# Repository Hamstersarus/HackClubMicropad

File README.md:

# HackClubMicropad

---

## Table of Contents

- [Overview](#overview)
- [Photos](#photos)
- [Bill of Materials](#bill-of-materials)

---

## Overview

The HackClub Micropad is a compact, USB-HID macropad intended for programmable shortcut input.
It was designed from scratch in KiCad and manufactured via JLCPCB. Firmware runs on CircuitPython.
It is a keybord with a programmable OLED screen, 6 keys, and a rotary encoder.
It is a fun, memorable, and beginner friendly productivity tool.

**Key features:**

- Seeed Studio XIAO RP2350 microcontroller
- Mechanical key switches (MX-compatible footprints)
- Rotary encoder with push-button
- Onboard NeoPixel (WS2812B) RGB indicator
- USB-C connectivity via the XIAO module
- 3D-printed enclosure (FDM, PLA)

---

## Photos

**PCB Top View**

**Assembled Board**

**Case**

---

### Bill of Materials

| Part Number | Description | Quantity | Ordering Location |
| :--- | :--- | :--- | :--- |
| 1597-102010550-ND | Seeed Studio XIAO RP2350 microcontroller (DIP) | 1 | [DigiKey](https://www.digikey.com/en/products/result?keywords=1597-102010550-ND) |
| 4809-EC11E15204A3-ND | EC11 rotary encoder with push-button, 5-pin | 1 | [DigiKey](https://www.digikey.com/en/products/detail/alps-alpine/EC11E15204A3/21721644) |
| 3086-MDOB128064V2V-YI-ND | SSD1306 OLED Screen | 1 | [DigiKey](https://www.digikey.com/en/products/detail/midas-displays/MDOB128064V2V-YI/20842029?s=N4IgTCBcDaIMwAYAcA2AtAWQCIHkBCAjGEgigCwBqYFaAmgJJoByWIAugL5A) |
| 1528-1541-ND | RGB LED with integrated controller (SK6812MINI) | 3 | [DigiKey](https://www.digikey.com/en/products/detail/adafruit-industries-llc/2686/5804107?s=N4IgTCBcDaIIwFYwA4C0iAsdUDkAiIAugL5A) |
| 1644-MX2A-E1NW-ND | Push button switch, normally open, 45° tilted | 6 | [DigiKey](https://www.digikey.com/en/products/detail/cherry-americas-llc/MX2A-E1NW/21738396?s=N4IgTCBcDaIIwDYAsSC0BZAGmAgqgonAHIDqqRAIiALoC%2BQA) |
| 1N4148FS-ND | 100V 0.15A standard switching diode, DO-35 | 7 | [DigiKey](https://www.digikey.com/en/products/detail/onsemi/1N4148/458603?s=N4IgTCBcDaIIwDkAsckA4BiBlAtAgIiALoC%2BQA) |
| 490-8808-ND | Unpolarized capacitor, 0.1uF | 5 | [DigiKey](https://www.digikey.com/en/products/detail/murata-electronics/RDER71E104K0K1H03B/4770963?s=N4IgTCBcDaICwE4AMBaAHGpaUDkAiIAugL5A) |
| 399-C324C106K3R5TA7301CT-ND | Unpolarized capacitor, 10uF | 2 | [DigiKey](https://www.digikey.com/en/products/detail/kemet/C324C106K3R5TA7301/12699356?s=N4IgTCBcDaIMwE4EFoDCcwBZUEYAMAbANJwBKArACoCCA7HHjqpcgHIAiIAugL5A) |
| 732-8825-1-ND | Polarized capacitor, 100uF | 2 | [DigiKey](https://www.digikey.com/en/products/result?keywords=732-8825-1-ND) |
| 56-CCF554K70FKE36CT-ND | Resistor, 4.7k | 2 | [DigiKey](https://www.digikey.com/en/products/detail/vishay-beyschlag-draloric-bc-components/CCF554K70FKE36/28262019?s=N4IgTCBcDaIKwDYC0BhFAxOcAsBpA7AAzq4CiAzAigCpIByAIiALoC%2BQA) |

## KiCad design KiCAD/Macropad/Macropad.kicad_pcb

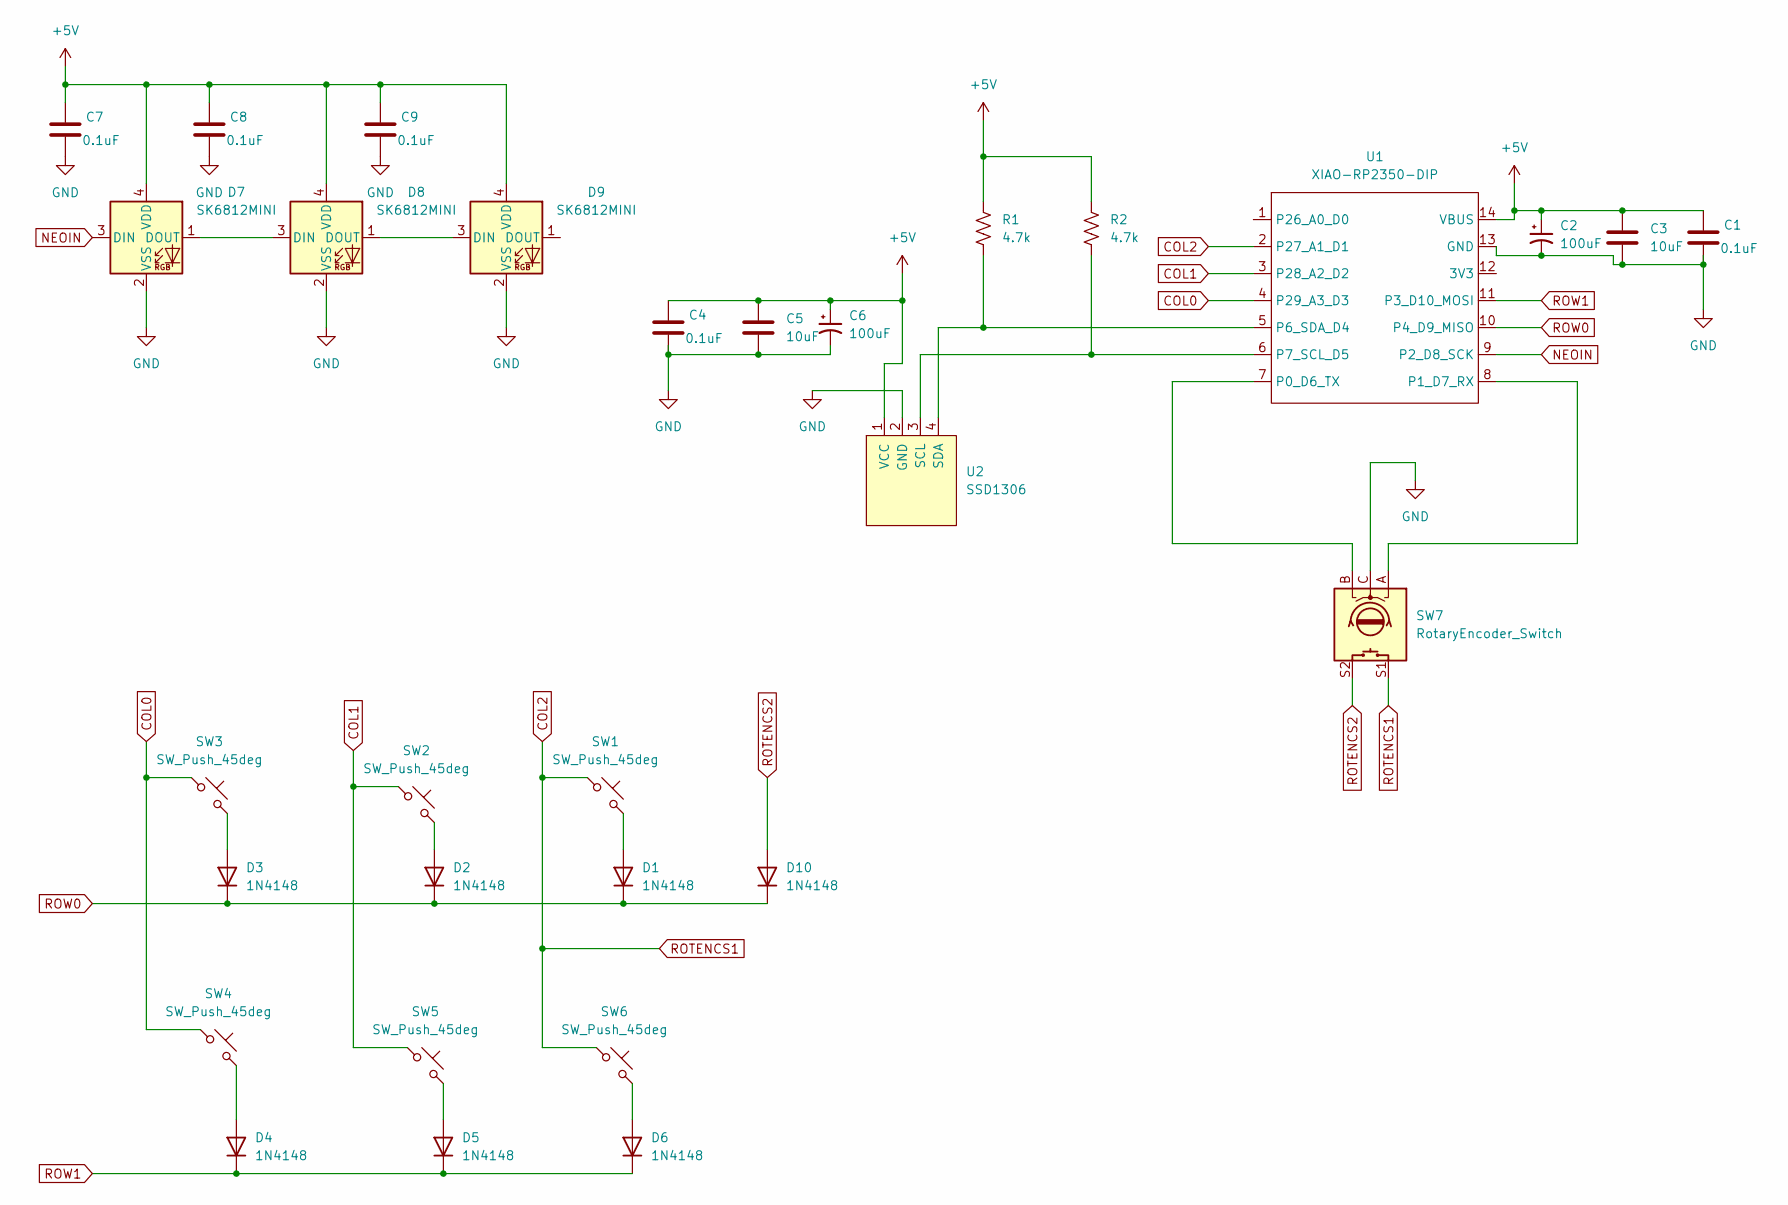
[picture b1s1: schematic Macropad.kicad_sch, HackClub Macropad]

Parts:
C1, C4, C7, C8, C9: 0.1uF; C_Disc_D3.8mm_W2.6mm_P2.50mm; Part_Number 490-8808-ND
C2, C6: 100uF; CP_Radial_Tantal_D6.0mm_P2.50mm; Part_Number 732-8825-1-ND
C3, C5: 10uF; C_Disc_D4.7mm_W2.5mm_P5.00mm; Part_Number 399-C324C106K3R5TA7301CT-ND
D1, D2, D3, D4, D5, D6, D10: 1N4148; D_DO-35_SOD27_P7.62mm_Horizontal; Part_Number 1N4148FS-ND
D7, D8, D9: SK6812MINI; LED_SK6812MINI_PLCC4_3.5x3.5mm_P1.75mm; Part_Number 1528-1541-ND
R1, R2: 4.7k; R_Axial_DIN0207_L6.3mm_D2.5mm_P7.62mm_Horizontal; Part_Number 56-CCF554K70FKE36CT-ND
SW1, SW2, SW3, SW4, SW5, SW6: SW_Push_45deg; SW_Cherry_MX_1.00u_PCB; Part_Number 1644-MX2A-E1NW-ND
SW7: RotaryEncoder_Switch; RotaryEncoder_Alps_EC11E-Switch_Vertical_H20mm; Part_Number 4809-EC11E15204A3-ND
U1: XIAO-RP2350-DIP; Part_Number 1597-102010550-ND
U2: SSD1306; MODULE_DM-OLED096-636; Part_Number 3086-MDOB128064V2V-YI-ND

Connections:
+5V: C1.1, C2.1, C3.1, C4.1, C5.1, C6.1, C7.1, C8.1, C9.1, D7.4 (VDD), D8.4 (VDD), D9.4 (VDD), R1.2, R2.2, U1.14 (VBUS), U2.1 (VCC)
COL0: SW3.1, SW4.1, U1.4 (P29_A3_D3)
COL1: SW2.1, SW5.1, U1.3 (P28_A2_D2)
COL2: SW1.1, SW6.1, SW7.S1, U1.2 (P27_A1_D1)
GND: C1.2, C2.2, C3.2, C4.2, C5.2, C6.2, C7.2, C8.2, C9.2, D7.2 (VSS), D8.2 (VSS), D9.2 (VSS), SW7.C, U1.13 (GND), U2.2 (GND)
NEOIN: D7.3 (DIN), U1.9 (P2_D8_SCK)
unnamed: D1.2 (A), SW1.2
unnamed: D2.2 (A), SW2.2
unnamed: D3.2 (A), SW3.2
unnamed: D4.2 (A), SW4.2
unnamed: D5.2 (A), SW5.2
unnamed: D6.2 (A), SW6.2
unnamed: D7.1 (DOUT), D8.3 (DIN)
unnamed: D8.1 (DOUT), D9.3 (DIN)
unnamed: SW7.B, U1.7 (P0_D6_TX)
unnamed: SW7.A, U1.8 (P1_D7_RX)
unnamed: R1.1, U1.5 (P6_SDA_D4), U2.4 (SDA)
unnamed: R2.1, U1.6 (P7_SCL_D5), U2.3 (SCL)
ROTENCS2: D10.2 (A), SW7.S2
ROW0: D1.1 (K), D2.1 (K), D3.1 (K), D10.1 (K), U1.10 (P4_D9_MISO)
ROW1: D4.1 (K), D5.1 (K), D6.1 (K), U1.11 (P3_D10_MOSI)

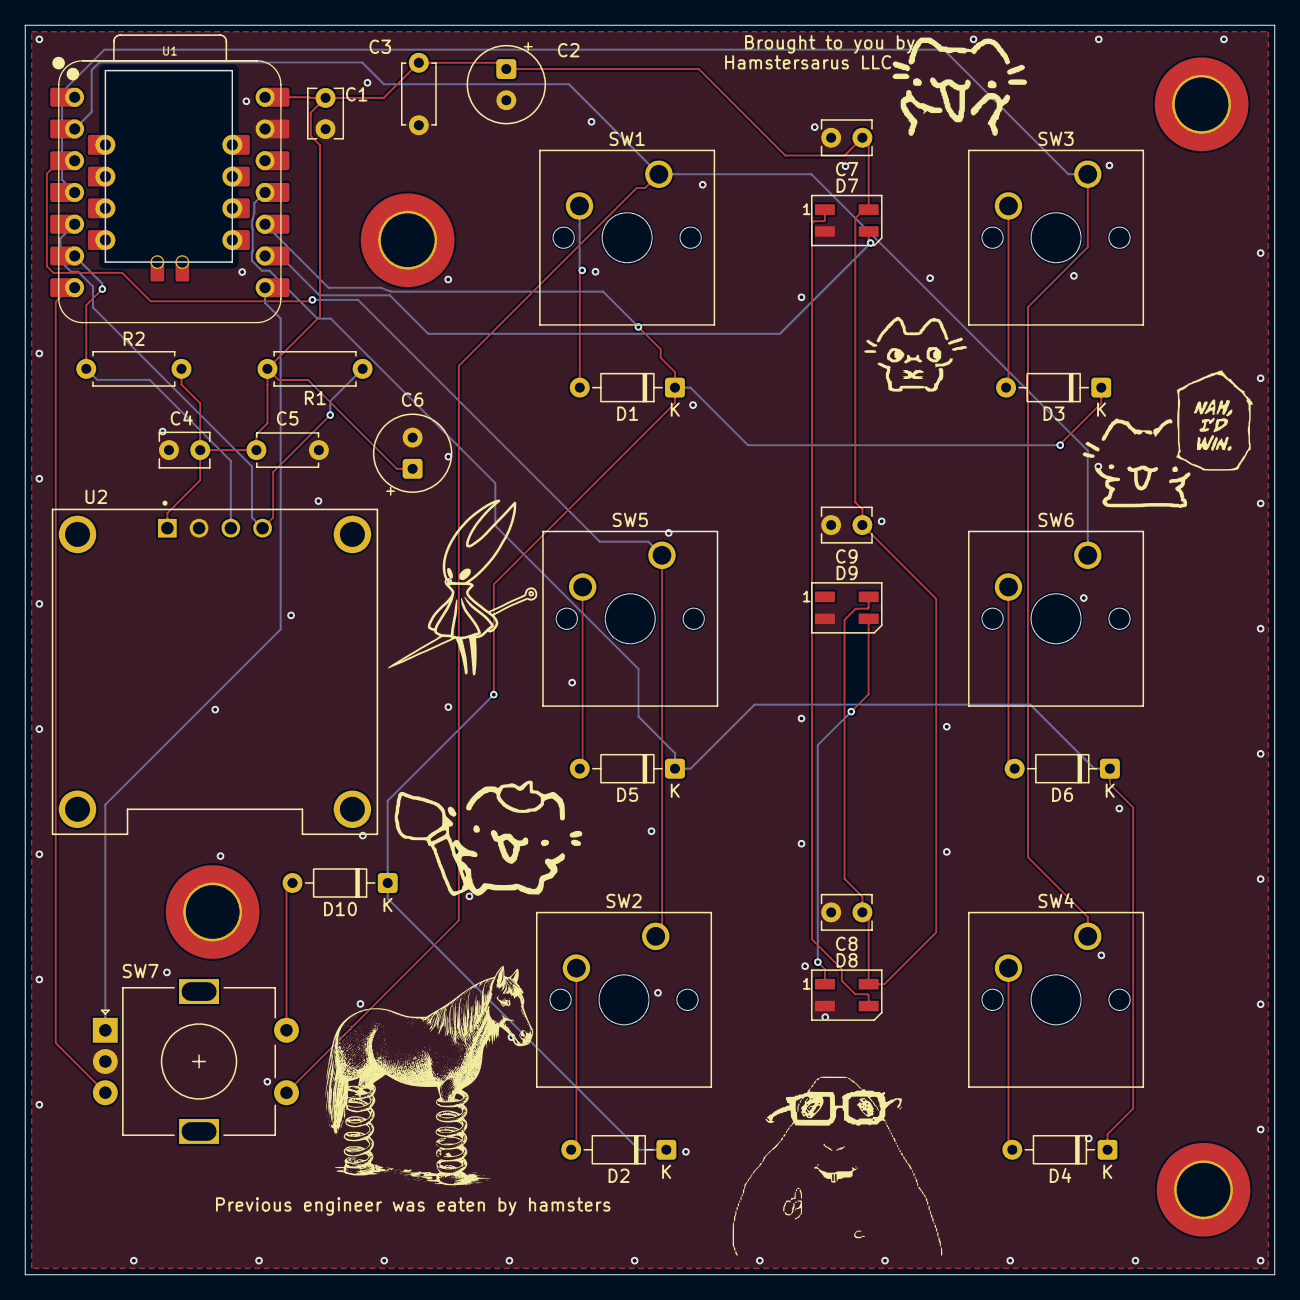
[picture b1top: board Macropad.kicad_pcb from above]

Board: 2 copper layers, 99.9 x 99.9 mm, 35 parts (0 on the bottom side), 21 nets.

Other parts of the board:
Brought to you by Hamstersarus LLC: LOGO
REF1, REF2, REF3, REF4: MountingHole_4.3mm_M4_DIN965_Pad_TopBottom

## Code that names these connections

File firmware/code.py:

## HackClub Macropad — KMK firmware with on-demand video playback
## Board: Seeed XIAO RP2350 (U1)
##
## Matrix (2 rows x 3 cols), diodes anode->switch->COL, cathode->ROW:
##   physical layout is 2 cols x 3 rows; see keymap comments for the mapping.
## Encoder (SW7): A=D6  B=D7  C=GND  (rotation = volume; turn-only)
## OLED (SSD1306, U2) I2C: SDA=D4  SCL=D5  addr=0x3C  (raw driver, 400kHz)
##
## Video: the top-left key sends "PLAY" over the USB *data* serial (enabled in
## boot.py). The host companion (host/play_companion.py) then streams 1024-byte
## OLED frames back over that channel while playing the audio on the computer.
## This module blits incoming frames to the OLED between matrix scans.

import board
import busio
import usb_cdc

from kmk.kmk_keyboard import KMKKeyboard
from kmk.keys import KC, make_key
from kmk.scanners import DiodeOrientation
from kmk.modules import Module
from kmk.extensions.media_keys import MediaKeys

import rotaryio

W, H = 128, 64
FRAME = W * H // 8  # 1024
ADDR = 0x3C
INIT = bytes([0xAE, 0xD5, 0x80, 0xA8, 0x3F, 0xD3, 0x00, 0x40, 0x8D, 0x14,
              0x20, 0x00, 0xA1, 0xC8, 0xDA, 0x12, 0x81, 0x7F, 0xD9, 0xF1,
              0xDB, 0x40, 0xA4, 0xA6, 0x2E, 0xAF])


class OLED:
    """Minimal raw SSD1306 128x64 driver — fast full-frame blits."""
    def __init__(self, scl, sda):
        self.i2c = busio.I2C(scl, sda, frequency=400_000)  # SSD1306 max
        while not self.i2c.try_lock():
            pass
        self.i2c.writeto(ADDR, b"\x00" + INIT)
        self._win = bytes([0x00, 0x21, 0, 127, 0x22, 0, 7])
        self._out = bytearray(1 + FRAME)
        self._out[0] = 0x40

    def show(self, buf):
        self.i2c.writeto(ADDR, self._win)
        self._out[1:] = buf
        self.i2c.writeto(ADDR, self._out)


def _load(path, default=b"\x00" * FRAME):
    try:
        with open(path, "rb") as f:
            d = f.read(FRAME)
        return d if len(d) == FRAME else default
    except OSError:
        return default


class VideoModule(Module):
    """Streams OLED frames from the USB data serial, between KMK scans."""
    def __init__(self):
        self.oled = OLED(board.D5, board.D4)
        self.splash = _load("/splash.bin")
        self.ser = usb_cdc.data
        self.frame = bytearray(FRAME)
        self.view = memoryview(self.frame)
        self.fill = 0

    def during_bootup(self, keyboard):
        self.oled.show(self.splash)

    def before_matrix_scan(self, keyboard):
        ser = self.ser
        if ser is not None and ser.in_waiting:
            self.fill += ser.readinto(self.view[self.fill:])
            if self.fill >= FRAME:
                self.oled.show(self.frame)
                self.fill = 0

    def after_matrix_scan(self, keyboard):
        pass

    def before_hid_send(self, keyboard):
        pass

    def after_hid_send(self, keyboard):
        pass

    def on_powersave_enable(self, keyboard):
        pass

    def on_powersave_disable(self, keyboard):
        pass


keyboard = KMKKeyboard()
keyboard.extensions.append(MediaKeys())

video = VideoModule()
keyboard.modules.append(video)

# Video control keys: signal the host companion over the USB data serial.
def _play(*args):
    if usb_cdc.data is not None:
        usb_cdc.data.write(b"PLAY\n")

def _stop(*args):
    if usb_cdc.data is not None:
        usb_cdc.data.write(b"STOP\n")

make_key(names=("VPLAY",), on_press=_play)
make_key(names=("VSTOP",), on_press=_stop)

# --- Key matrix ---
keyboard.col_pins = (board.D3, board.D2, board.D1)   # COL0, COL1, COL2
keyboard.row_pins = (board.D9, board.D10)            # ROW0, ROW1
keyboard.diode_orientation = DiodeOrientation.COL2ROW

# --- Encoder (volume), hardware-decoded --------------------------------
# rotaryio counts in the RP2350's PIO, so turns are never missed even when a
# video blit stalls the main loop (KMK's software GPIO encoder mis-decodes
# there). We tap VOLU/VOLD from the accumulated count, one step per scan.
class HWVolumeEncoder(Module):
    def __init__(self, pin_a, pin_b, cw=KC.VOLU, ccw=KC.VOLD):
        self.enc = rotaryio.IncrementalEncoder(pin_a, pin_b)
        self.cw = cw
        self.ccw = ccw
        self.last = 0
        self.pending = 0

    def during_bootup(self, keyboard):
        self.last = self.enc.position

    def before_matrix_scan(self, keyboard):
        pos = self.enc.position
        if pos != self.last:
            self.pending += pos - self.last
            self.last = pos
        if self.pending > 0:
            self.pending -= 1
            keyboard.tap_key(self.cw)
        elif self.pending < 0:
            self.pending += 1
            keyboard.tap_key(self.ccw)

    def after_matrix_scan(self, keyboard): pass
    def before_hid_send(self, keyboard): pass
    def after_hid_send(self, keyboard): pass
    def on_powersave_enable(self, keyboard): pass
    def on_powersave_disable(self, keyboard): pass

keyboard.modules.append(HWVolumeEncoder(board.D6, board.D7))

# --- Keymap ---
# Physical 2 cols x 3 rows. Electrical scan order is row0 then row1, col0..col2.
#   top-left = PLAY video       top-right = STOP video
#   mid-left = c                mid-right = d
#   bot-left = e                bot-right = f
keyboard.keymap = [
    [
        # ROW0:  SW3(top-right)   SW2(bot-left)   SW1(top-left)
        KC.VSTOP,        KC.E,           KC.VPLAY,
        # ROW1:  SW4(bot-right)   SW5(mid-left)   SW6(mid-right)
        KC.F,            KC.C,           KC.D,
    ],
]

if __name__ == '__main__':
    keyboard.go()

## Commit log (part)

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2026-01-31 Initial commit of BOM spreadsheet and datasheets.
2026-01-31 Made changes to parts list, added 3D model and KiCad sch and pcb symbols for the Raspberry Pi Pico H.
2026-02-16 Created schematic symbol for rp2040 cpu and added its libraries.
2026-02-16 Added roatary encoder and libraries.
2026-02-22 Updated schematic with push buttons and rotary encoder.
2026-02-23 Added majority of components to schematic. :)
2026-02-23 Added diodes and ports, finished schematic :D.
2026-02-24 Added footprints for rotary encoder and rp2040.
2026-02-25 Made updates to BOM.
2026-03-31 Initial candidate for layout
2026-03-31 Finished board wiring, layout, silkscreen, removed unneeded files, added case 3D model.
2026-03-31 Added some tester code
2026-04-01 Update README.md
    Wrote the README, everything except a 3D model of the board in the case.
2026-04-01 Update README.md
    Added the screenshot of the board in the case.
2026-04-01 Added assembly: case+board
2026-04-20 Changed pictures for the case and the assembled view
2026-04-20 Fixed case
2026-06-03 Fixed some shorts in the matrix.
2026-06-08 Updated schematic and layout with new EC11 rotary encoder.
2026-06-13 Reorganize XIAO footprints into .pretty library
2026-06-13 Add v001 Gerber manufacturing output
2026-06-13 Update layout, schematic, and interactive BOM with part numbers
2026-06-13 Updated README DOM and PCB top-view image
2026-06-22 Fixed a crossed wire issue and an issue with my microcontroller.
